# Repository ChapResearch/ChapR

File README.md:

# ChapR
The ChapR is a patented remote for controlling FTC, FLL, and FRC robots without a PC. It allows teams to easily set up drive practices and run autonomous programs without bothering the programmer(s) or fighting over the few PCs available. Created in 2013, it has been “sold” to hundreds of teams all over the world, using the “profits” to fund free ChapRs for teams in need. For more information on sales and usage of the device, see [the project website](http://thechapr.com). For more information on the creation of the device, see its [project page](http://chapresearch.com/?page_id=868).

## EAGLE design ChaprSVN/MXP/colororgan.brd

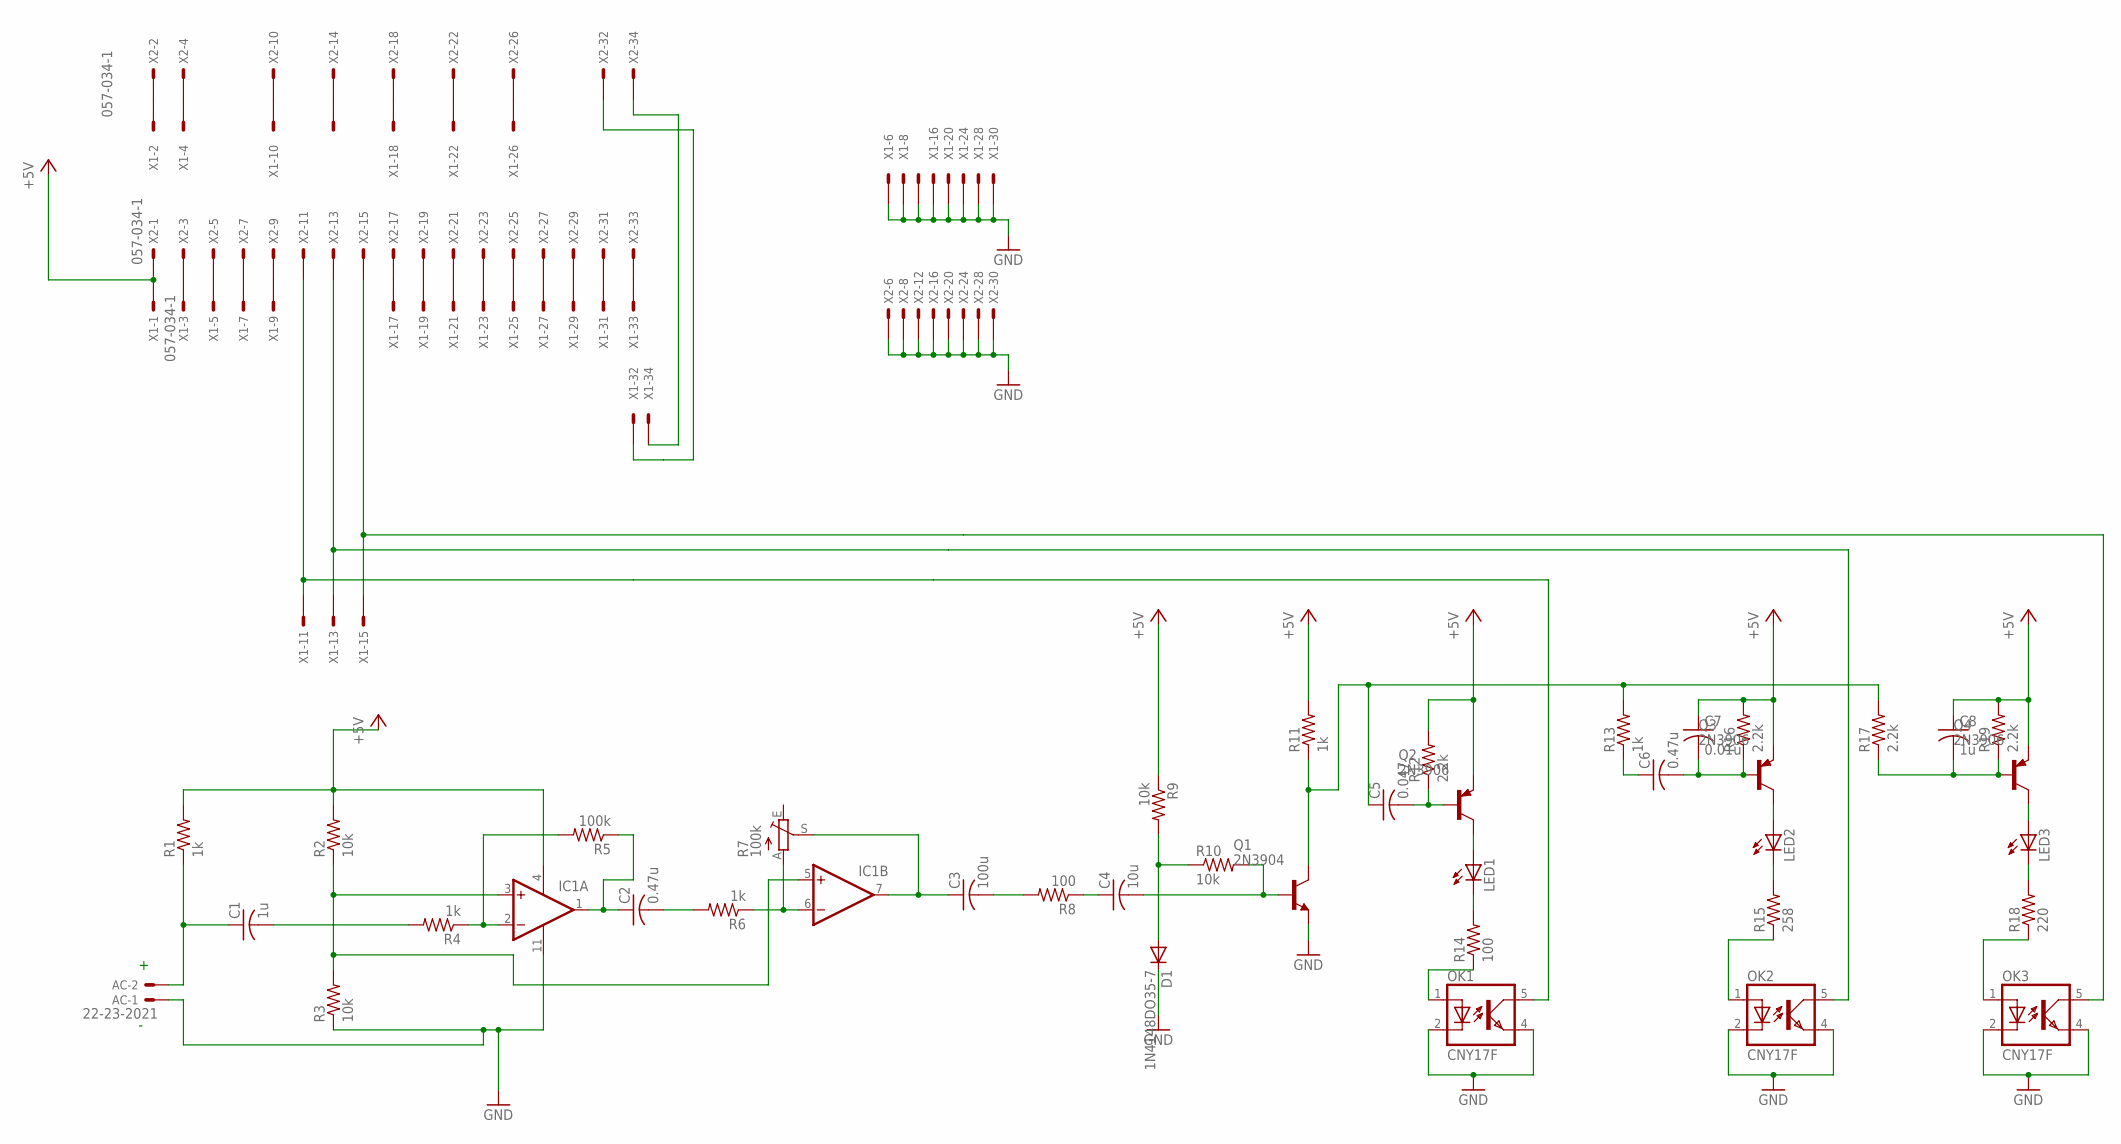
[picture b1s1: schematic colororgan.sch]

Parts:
AC: 22-23-2021
C1, C8: 1u; C025-050X050
C2, C6: 0.47u; C025-050X050
C3: 100u; C025-050X050
C4: 10u; C025-050X050
C5: 0.047; C025-050X050
C7: 0.01u; C025-050X050
D1: 1N4148DO35-7; DO35-7
IC1: LMV324THR; DIL14
LED1, LED2, LED3: LED3MM
OK1, OK2, OK3: CNY17F; DIL06
Q1: 2N3904; TO92
Q2, Q3, Q4: 2N3906; TO92
R1, R4, R6, R11, R13: 1k; 0207/10
R2, R3, R9, R10: 10k; 0207/10
R5: 100k; 0207/10
R7: 100k; RS3
R8, R14: 100; 0207/10
R12, R16, R17, R19: 2.2k; 0207/10
R15: 258; 0207/10
R18: 220; 0207/10
X1, X2: 057-034-1

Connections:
+5V: C7.1, C8.1, IC1.4 (V+), Q2.3 (E), Q3.3 (E), Q4.3 (E), R1.2, R2.2, R9.1, R11.2, R12.2, R16.2, R19.2, X1.1, X2.1
GND: AC.1, D1.C, IC1.11 (V-), OK1.2 (C), OK1.4 (EMIT), OK2.2 (C), OK2.4 (EMIT), OK3.2 (C), OK3.4 (EMIT), Q1.3 (E), R3.1, X1.6, X1.8, X1.12, X1.16, X1.20, X1.24, X1.28, X1.30, X2.6, X2.8, X2.12, X2.16, X2.20, X2.24, X2.28, X2.30
unnamed: AC.2, C1.1, R1.1
unnamed: D1.A, R9.2, R10.1
unnamed: C1.2, R4.2
unnamed: IC1.3 (+IN), IC1.5 (+IN), R2.1, R3.2
unnamed: IC1.2 (-IN), R4.1, R5.2
unnamed: C2.1, IC1.1 (OUT), R5.1
unnamed: C2.2, R6.2
unnamed: IC1.6 (-IN), R6.1, R7.A
unnamed: C4.2, Q1.2 (B), R10.2
unnamed: C3.1, IC1.7 (OUT), R7.S
unnamed: C3.2, R8.2
unnamed: C4.1, R8.1
unnamed: C5.1, Q1.1 (C), R11.1, R13.2, R17.2
unnamed: C5.2, Q2.2 (B), R12.1
unnamed: OK1.1 (A), R14.1
unnamed: LED1.K (C), R14.2
unnamed: LED1.A, Q2.1 (C)
unnamed: C6.1, R13.1
unnamed: C6.2, C7.2, Q3.2 (B), R16.1
unnamed: OK1.5 (COL), X1.11, X2.11
unnamed: LED2.A, Q3.1 (C)
unnamed: LED2.K (C), R15.2
unnamed: OK2.1 (A), R15.1
unnamed: OK2.5 (COL), X1.13, X2.13
unnamed: C8.2, Q4.2 (B), R17.1, R19.1
unnamed: LED3.A, Q4.1 (C)
unnamed: LED3.K (C), R18.2
unnamed: OK3.1 (A), R18.1
unnamed: OK3.5 (COL), X1.15, X2.15
unnamed: X1.34, X2.34
unnamed: X1.32, X2.32
unnamed: X1.2, X2.2
unnamed: X1.4, X2.4
unnamed: X1.10, X2.10
unnamed: X1.14, X2.14
unnamed: X1.33, X2.33
unnamed: X1.3, X2.3
unnamed: X1.5, X2.5
unnamed: X1.7, X2.7
unnamed: X1.9, X2.9
unnamed: X1.17, X2.17
unnamed: X1.19, X2.19
unnamed: X1.21, X2.21
unnamed: X1.23, X2.23
unnamed: X1.25, X2.25
unnamed: X1.27, X2.27
unnamed: X1.29, X2.29
unnamed: X1.31, X2.31
unnamed: X1.18, X2.18
unnamed: X1.22, X2.22
unnamed: X1.26, X2.26

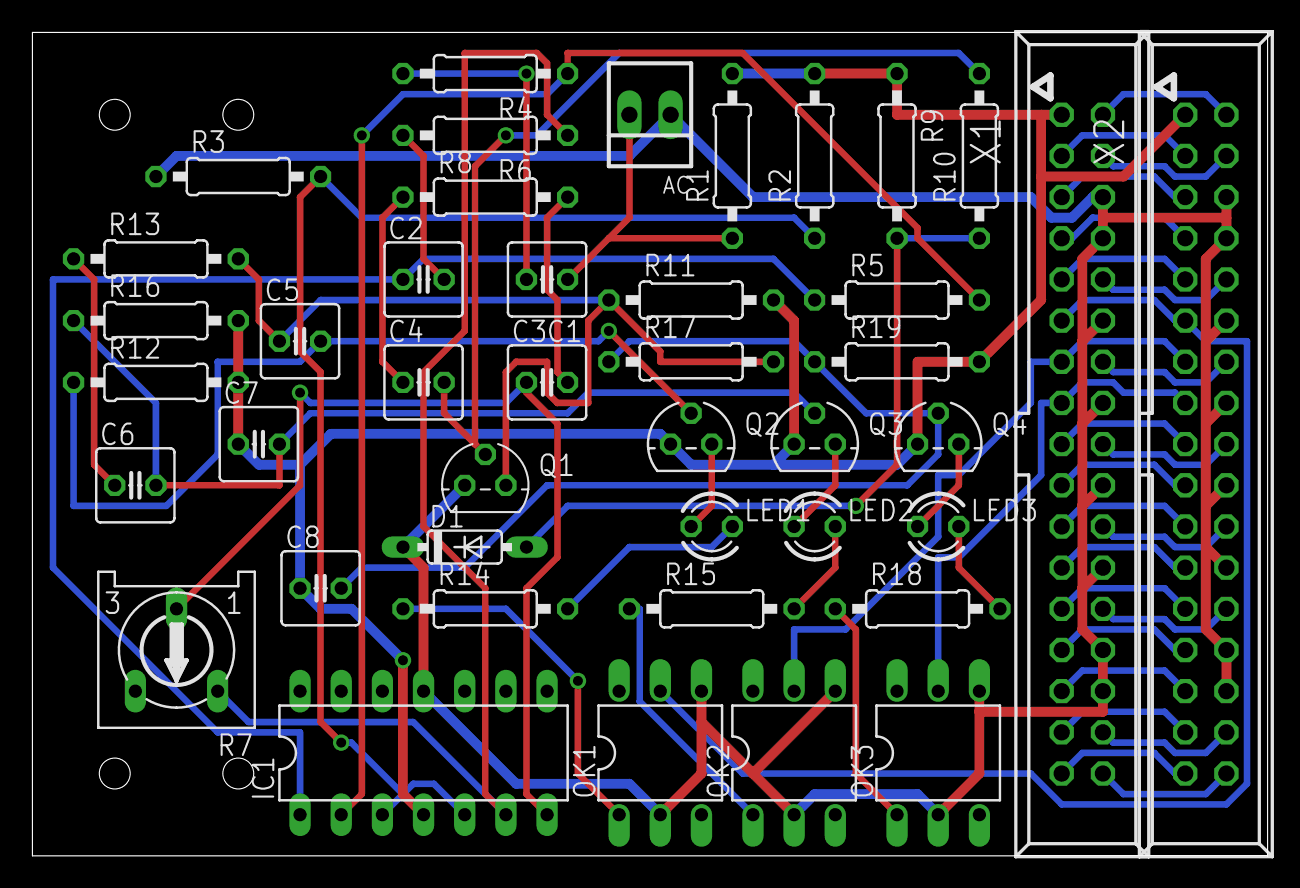
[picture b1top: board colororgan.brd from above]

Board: 2 copper layers, 76.2 x 50.8 mm, 42 parts (0 on the bottom side), 53 nets.

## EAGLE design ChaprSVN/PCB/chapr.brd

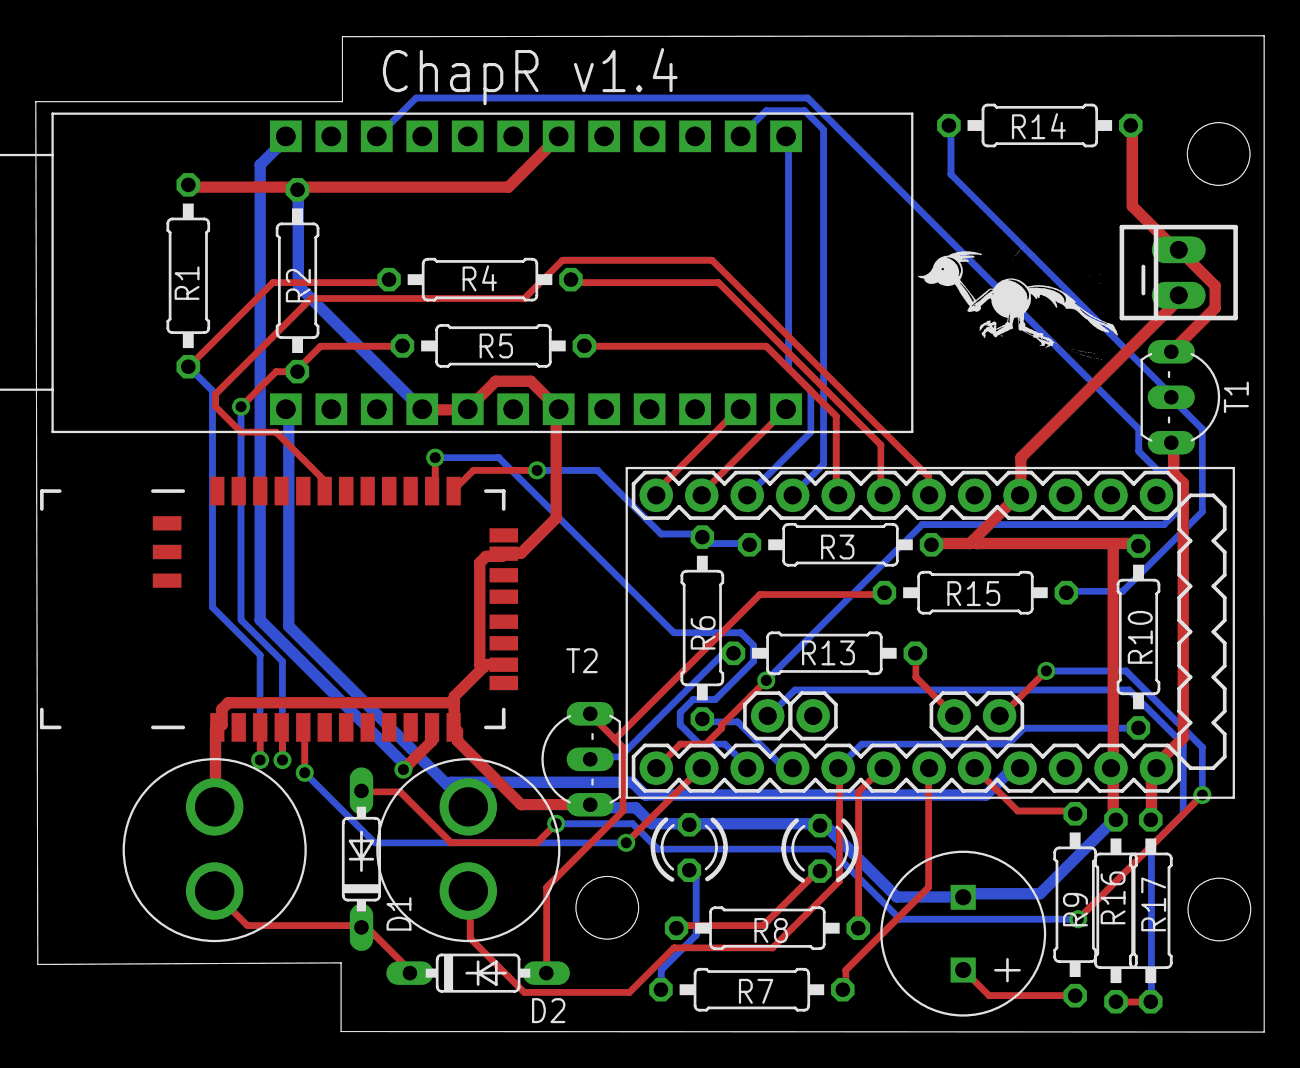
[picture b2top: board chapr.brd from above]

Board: 2 copper layers, 68.6 x 55.6 mm, 28 parts (0 on the bottom side), 33 nets.

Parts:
-: 9v power; 22-23-2021
ARDUINO: PROMININOHEADER
D1, D2: 1N4148; DO35-7
LED1: LED3MM
M2: RN42 Module; RN41
PB1: PUSHBUTTON; 2-PIN-PUSHBUTTON
PB2: BUTTON; 2-PIN-PUSHBUTTON
PWR-LED: LED3MM
R1, R2, R3, R14: 19.1k; 0207/10
R4, R5, R6, R10, R13: 10k; 0207/10
R7, R8: 470; 0207/10
R9: 100; 0207/10
R15: 1.5k; 0207/10
R16, R17: 24K; 0207/10
T1: 3906; TO92-EBC
T2: 3904; TO92-EBC
U$1: V2DIP2
U$2: SPEAKER

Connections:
+3V3: M2.11, U$1.P$24
+5V: ARDUINO.VCC, PB1.P$1, U$1.P$1
+9V: -.2, R14.2, T1.E
GND: -.1, ARDUINO.GND, ARDUINO.GND2, LED1.K, M2.1, M2.12, M2.28, M2.29, PB2.P$1, PWR-LED.K, R1.1, R2.1, R3.1, R10.1, R16.2, T2.E, U$1.P$4, U$1.P$5, U$1.P$7, U$1.P$18, U$2.-
unnamed: R14.1, R15.1, T1.B
unnamed: ARDUINO.D10, U$1.P$22
unnamed: ARDUINO.D13, R6.2
unnamed: ARDUINO.D12, M2.14
unnamed: ARDUINO.D11, M2.5
unnamed: M2.3, R1.2, R4.1
unnamed: M2.4, R2.2, R5.1
unnamed: ARDUINO.D5, R5.2
unnamed: M2.13, R3.2, R6.1
unnamed: ARDUINO.D6, U$1.P$14
unnamed: ARDUINO.D7, U$1.P$13
unnamed: ARDUINO.D8, U$1.P$12
unnamed: ARDUINO.D9, U$1.P$11
unnamed: ARDUINO.D4, R4.2
unnamed: ARDUINO.D3, M2.19
unnamed: PWR-LED.A, R7.1
unnamed: LED1.A, R8.1
unnamed: ARDUINO.A2, R7.2
unnamed: R9.1, U$2.+
unnamed: ARDUINO.A1, R8.2
unnamed: ARDUINO.A3, R9.2
unnamed: ARDUINO.RAWV, R17.1, T1.C
unnamed: ARDUINO.A0, PB1.P$2, R10.2
unnamed: D2.A, R15.2, T2.C
unnamed: R13.1, T2.B
unnamed: D1.C, D2.C, PB2.P$2
unnamed: ARDUINO.A5, D1.A
unnamed: ARDUINO.A4, R13.2
unnamed: ARDUINO.A6, R16.1, R17.2

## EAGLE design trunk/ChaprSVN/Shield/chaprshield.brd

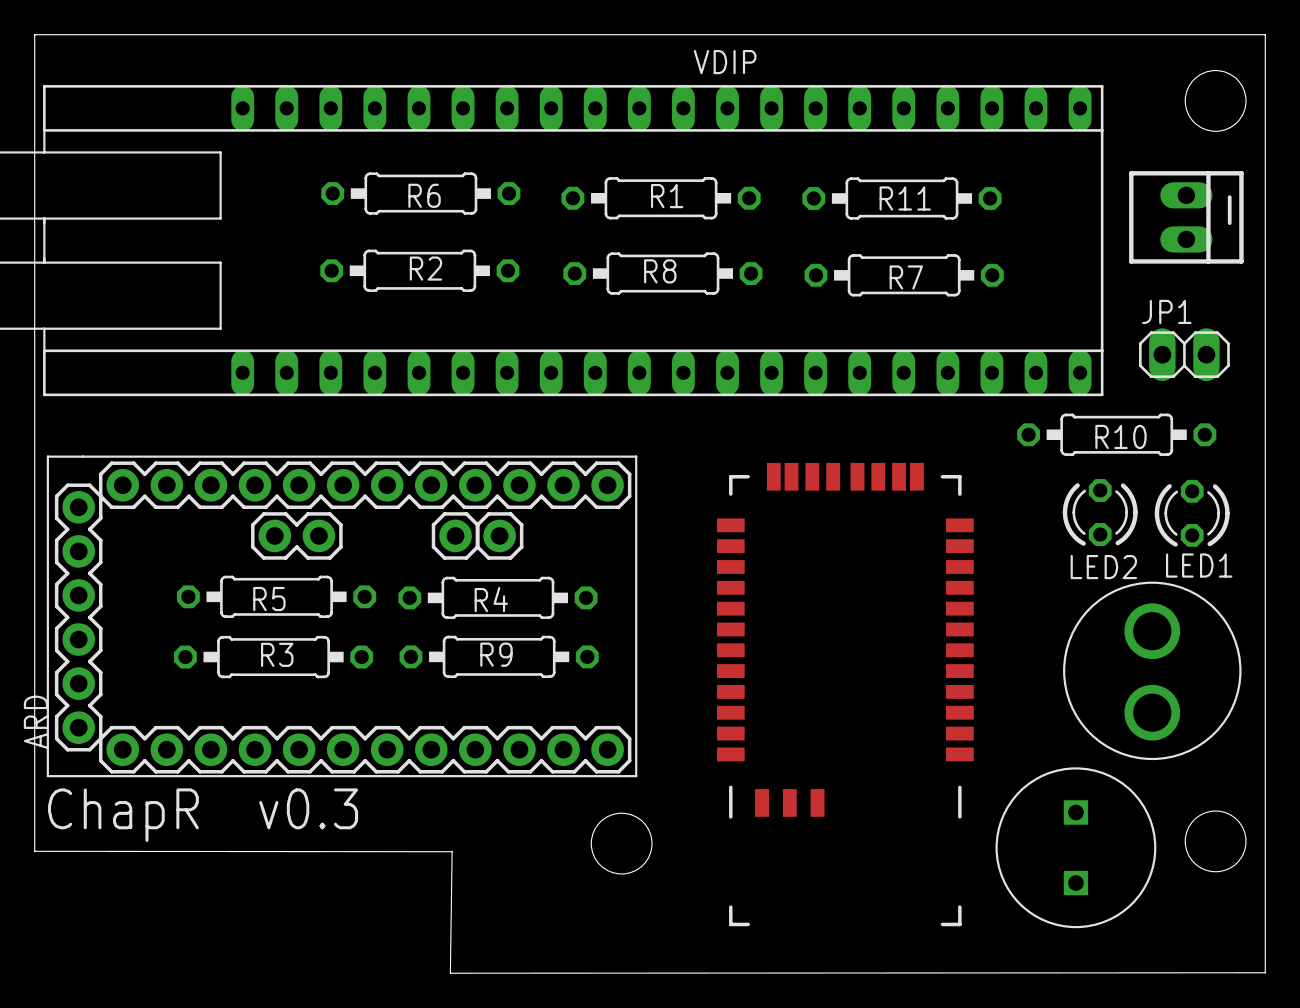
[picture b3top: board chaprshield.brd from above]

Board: 2 copper layers, 70.9 x 54.1 mm, 20 parts (0 on the bottom side), 26 nets, no tracks yet.

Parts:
-: 9v power; 22-23-2021
ARD: PROMINI
JP1: 1X02
LED1, LED2: LED3MM
M2: RN42 Module; RN41
PB1: PUSHBUTTON; 2-PIN-PUSHBUTTON
R1, R2, R3: 19.1k; 0207/10
R4, R5, R6, R10, R11: 10k; 0207/10
R7, R8: 470; 0207/10
R9: 100; 0207/10
U$2: SPEAKER
VDIP: VDIP2

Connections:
3.3V: JP1.2, M2.11, VDIP.32, VDIP.38, VDIP.39
+9V: -.2, ARD.RAWV
GND: -.1, ARD.GND, ARD.GND2, LED1.K, LED2.K, M2.1, M2.12, M2.28, M2.29, R1.1, R2.1, R3.1, R10.1, R11.1, U$2.-, VDIP.12, VDIP.13, VDIP.15, VDIP.26
unnamed: ARD.VCC, PB1.P$1, VDIP.2, VDIP.3, VDIP.9
unnamed: ARD.D10, VDIP.30
unnamed: ARD.D13, R6.2
unnamed: ARD.D12, M2.14
unnamed: ARD.D11, M2.5
unnamed: M2.3, R1.2, R4.1
unnamed: M2.4, R2.2, R5.1
unnamed: ARD.D5, R5.2
unnamed: M2.13, R3.2, R6.1
unnamed: ARD.D9, VDIP.18
unnamed: ARD.D8, VDIP.17
unnamed: ARD.D7, VDIP.16
unnamed: ARD.D6, VDIP.14
unnamed: ARD.D4, R4.2
unnamed: ARD.D3, M2.19
unnamed: LED2.A, R7.1
unnamed: LED1.A, R8.1
unnamed: ARD.A2, R7.2
unnamed: R9.1, U$2.+
unnamed: ARD.A1, R8.2
unnamed: ARD.A3, R9.2
unnamed: JP1.1, M2.22, R11.2
unnamed: ARD.A0, PB1.P$2, R10.2

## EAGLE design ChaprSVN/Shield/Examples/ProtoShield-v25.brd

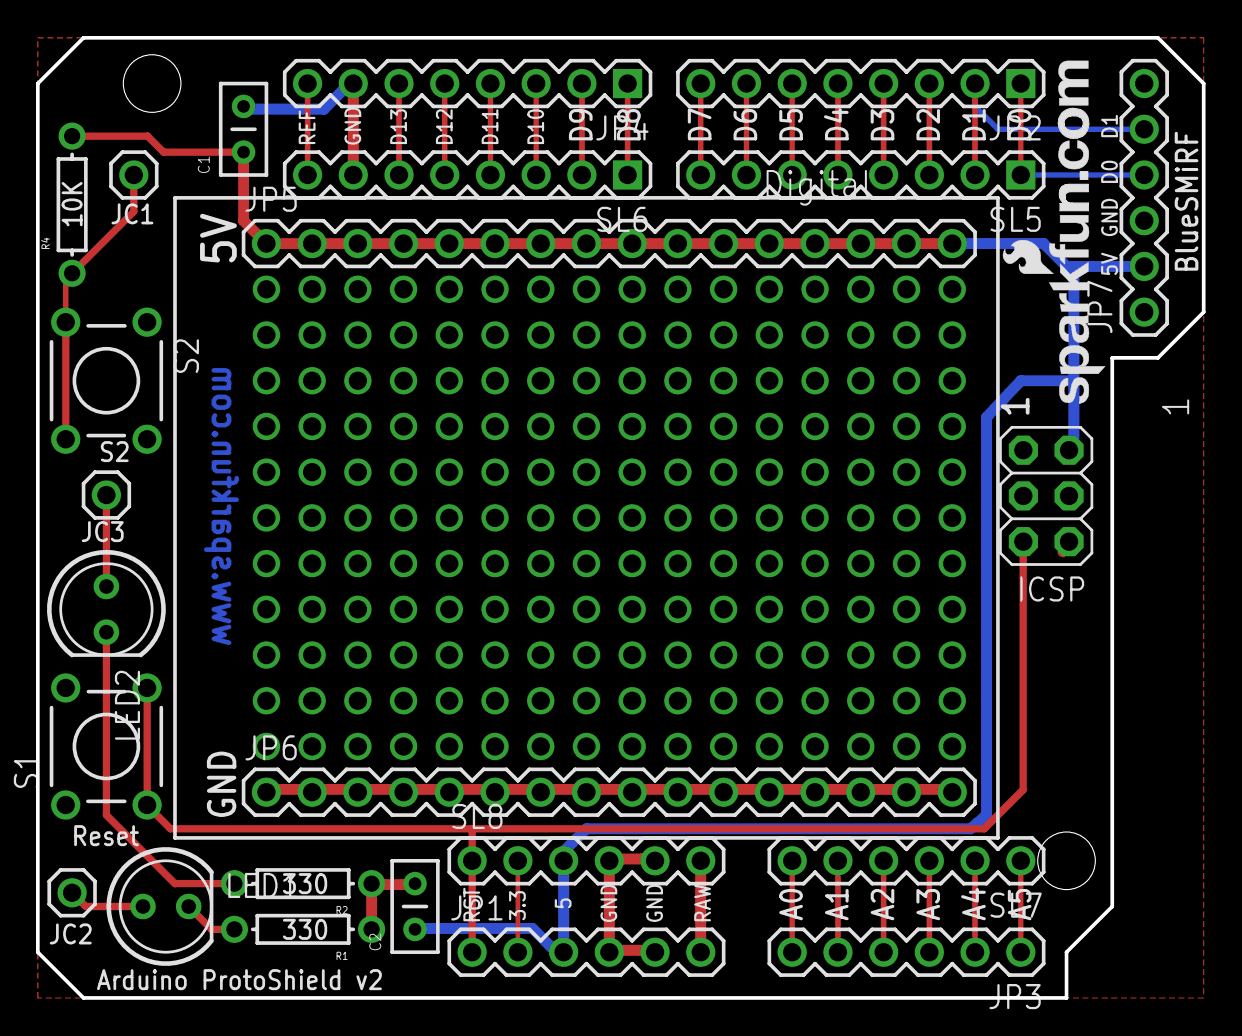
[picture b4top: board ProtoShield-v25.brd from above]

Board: 2 copper layers, 64.8 x 53.3 mm, 27 parts (0 on the bottom side), 31 nets.

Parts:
BB1: BREADBOARDMINI; BREADBOARD-MINI
C1, C2: 0.1uF; CAP-PTH-SMALL2
ICSP: ICSP; 2X03
JC1, JC2, JC3: M01PTH; 1X01
JP1: Power; 1X06
JP2: Digital1; 1X08
JP3: Analog; 1X06
JP4: Digital2; 1X08
JP5, JP6: M16PTH; 1X16
JP7: BlueSMiRF; 1X06
LED1, LED2: LED5MM
R1, R2: 330; AXIAL-0.3
R4: 10K; AXIAL-0.3
S1: Reset; TACTILE-PTH
S2: TACTILE-PTH
SL5, SL6: 1X08
SL7, SL8: 1X06
U$1: LOGO-SFENEW; SFE-NEW-WEBLOGO
U$2: CREATIVE_COMMONS

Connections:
3.3V: JP1.2, SL8.2
5V: C1.1, C2.1, ICSP.2, JP1.3, JP5.1, JP5.2, JP5.3, JP5.4, JP5.5, JP5.6, JP5.7, JP5.8, JP5.9, JP5.10, JP5.11, JP5.12, JP5.13, JP5.14, JP5.15, JP5.16, JP7.2, R4.P$2, SL8.3
A0: JP3.6, SL7.6
A1: JP3.5, SL7.5
A2: JP3.4, SL7.4
A3: JP3.3, SL7.3
A4: JP3.2, SL7.2
A5: JP3.1, SL7.1
AREF: JP4.8, SL6.8
D2: JP2.3, SL5.3
D3: JP2.4, SL5.4
D4: JP2.5, SL5.5
D5: JP2.6, SL5.6
D6: JP2.7, SL5.7
D7: JP2.8, SL5.8
D8: JP4.1, SL6.1
D9: JP4.2, SL6.2
D10: JP4.3, SL6.3
D11: JP4.4, SL6.4
D12: JP4.5, SL6.5
D13: JP4.6, SL6.6
GND: C1.2, C2.2, ICSP.6, JP1.4, JP1.5, JP4.7, JP6.1, JP6.2, JP6.3, JP6.4, JP6.5, JP6.6, JP6.7, JP6.8, JP6.9, JP6.10, JP6.11, JP6.12, JP6.13, JP6.14, JP6.15, JP6.16, JP7.3, R1.P$1, R2.P$1, S1.1, S1.2, S2.1, S2.2, SL6.7, SL8.4, SL8.5
unnamed: JC1.1, R4.P$1, S2.3, S2.4
unnamed: LED1.K, R1.P$2
unnamed: LED2.K, R2.P$2
unnamed: JC2.1, LED1.A
unnamed: JC3.1, LED2.A
RESET: ICSP.5, JP1.1, S1.3, S1.4, SL8.1
RX: JP2.1, JP7.4, SL5.1
TX: JP2.2, JP7.5, SL5.2
VIN: JP1.6, SL8.6

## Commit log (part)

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2014-05-20 Removed references to MODE coming from the main .ino loop. In personality 1 mode wasn't used anyway.
2014-05-20 Refactored mode stuff (now reads from EEPROM for normal setting and changes appropriately for matchMode)
2014-05-20 Removed references to the usermode (teleop/auto) leaving that for the personalities to deal with. It is still in EEPROM (settings), however.
2014-05-20 Finished refactoring.
2014-05-20 Got rid of all usermode stuff
2014-05-20 Refactoring done for real...maybe?
2014-05-20 Removed the zombie mode that we no longer used. Note that the code is in a NOTDEF in VDIP.cpp and BT.cpp so some future person can see how to enter zombie mode if they want.
2014-05-21 Adjusted The ChapR.vi to account for the new packet structure (incorporates analog and digital inputs).
2014-06-05 Implemented the match cycling in personality 0 and 3. Also added the rough drafts of documentation stuff. The Match Cycling Diagram.pptx is just meant to give an idea of whether or not we could make 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
2014-06-05 Moved the ChapR stuff out of this folder (so it would all be in one place, called by all test programs). NOT BEEN TESTED.
2014-06-05 ChapR Test files and ChapR Code in its own folder.
2014-06-05 Commented the ChapR Test code.
2014-06-06 Fixed the button translating in the ChapR.vi. Also made a small change to ChapR Test for debugging matchMode.
2014-06-06 Changed cRIO calls to require booleans specifying enable/mode for sending data to the cRIO (as opposed to having defines for the commands).
2014-06-06 Updated to remove the button from the Loop() call.
2014-06-07 Updated the Loop() function to NOT have the button. It doesn't affect this personality in any way.
2014-06-07 Removed the button from the Loop() function and recoded appropriately to use the "enabled" member of the personality object.
2014-06-10 Added new stuff to the back of my head.txt and some sketchy NXT Remote/Old Remote/Copy of client.c stuff...
2014-06-10 Combined the code for personalities 0 and 2 to save code space. 2 is just like 0 except that the action button toggles enabled.
2014-08-26 Added a ProMini version without the 6 pin header. The silk screen is still there so that it is easy to appropriately orient the ProMini, but this version doesn't cause the holes to be drilled, provid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
2014-08-26 Removed the extraneous library backup files.
2014-08-26 Used the new ProMini without the top 6 pins. Created AutoRouter and DesignRule files for repeatable routing. Added clearance between vias and pads so we don't have to post-process the routes.
2014-10-19 Added the ChapR Soldering Station List.doc
2014-10-25 Added ChapR Kit Instructions.docx
2014-11-05 Fixed a minor bug with the output saying the wrong status message.
2014-11-05 added LATEST (and hopefully last) endcap, with ALL relevant files
2014-12-19 Added the "chaprd" program for driving FRC bots with roboRIO.
2014-12-24 Added the SparkFun Blog Post.docx
2014-12-24 Added the full translation for chaprd.c
2014-12-27 latest version of chaprd - NOT working yet
2014-12-29 Added the Chap Research 2015 Kickoff Presentation.pptx.
2014-12-30 Latest (minor) edits.
2015-01-02 Made it so the daemon could start on boot. Still a problem with ejecting and re-plugging in the FirePlug.
2015-01-04 Ben's first cut at Eagle versions of the BeatBoard MXP board.
2015-01-04 A few changes for ease of reading. added 5v to the upward bound MXP connector.
2015-01-05 Added Makefile for building of the install file. Added install file template.
2015-01-06 It the Solo now works like it used to on the new board. It can detect different game modes now.
2015-01-07 Took the sleep statement out of the daemon. Adjusted the install shell script so that it doesn't change the permissions of the entire init.d (aka preventing lvrt from running important stuff).
2015-01-10 The latest fiddling around with getting the VDIP to set the BAUD rate on the FirePlug
2015-01-12 V2DIP2 Source as a reference for the VDIP source - this only has VDAP for now
2015-01-14 Added the Chap Research 2015 Kickoff Presentation and made slight modifications to the SparkFun Blog Post.docx
2015-01-14 Made minor edits to the QA info.
2015-01-15 The score reader works for 6 digit numbers... but it has a little problem with 5 digits.(should be relatively easy to fix though)
2015-01-16 Michael did something? Potentially bug testing. Evidently very minor.
2015-01-17 added a space
2015-01-18 added doPiano and sounds for it
2015-01-19 Made the final changes (this is the version that was submitted).
2015-01-19 The score playing system works. Just need to add sound files fore ten, eleven, and twelve.
2015-01-20 fixed wrong case vdip.h
2015-01-20 FirePlug programming integration - as well as a few optimizations
2015-01-20 forgot to update this when I updated VDIP.cpp
2015-01-20 added default in switch to quite compiler - an actually saved 14 bytes
2015-01-20 took out superficial .mp3 extension
2015-01-20 Made minor changes to fix the unsigned vs signed compiler warnings
2015-01-21 Added steps to test the new features of software v2.0
2015-01-21 Added piano mode
2015-01-21 saved a few bytes of memory by making explicit delay call
2015-01-21 fixed a few more compiler warnings
2015-01-22 added wiring diagram
2015-01-22 NOT FULLY WORKING - added matchmode and personality 0/2 implementation of it - turned off personality 3 for now
2015-01-22 personality 0/2 working first version of matchmode - not fully tested, but in pretty good shape.
2015-01-22 A couple fixes to personality 0/2, and a space rewrite of personality 1.
2015-01-23 Re-added the FTC LabView testing program (called teleop.vi).
2015-01-24 Make minor changes.
2015-01-25 Finished the Wiring Diagram.pptx
2015-01-27 renamed install file
2015-02-02 Added in boardBringUp and made memory optimization changes.
2015-02-03 Made minor edits to fix the bug about the ChapR not disabled when disconnected.
2015-02-04 Adjusted the wires that go to the analog pins on the Arduino.
2015-02-07 Added the Testing Programs and the end_plate stuff.
2015-02-07 The final copy that was discussed with Coach Eric, Coach Morgan, Rachel Gardner, Scott Gardner and Michael Huang.
2015-02-07 The "diff" feature doesn't work, so I'm not sure what changed, but ok. Probably something very small.
2015-02-08 Made the Chap Research Description.docx more aesthetically pleasing.
2015-02-08 Added the Arduino code for running the RN42 tester.
2015-02-10 Changes to bring the code under 30k bytes. Mostly to setup strings and the analog values.
2015-02-10 Added "!" starts up board bringup.
2015-02-10 Added RN42 test program that can cause an RN42 to print out version number on a completed ChapR - though you have to have a logic analyzer to see it!
2015-02-12 A bug in new magic new is still there. When played, the arduino senses a fruit being touched before you can touch the correct fruit.
2015-02-12 The latest and greatest almost working one.
2015-02-12 Done: analog triggers of Xbox 360 always send 0
    FTC personalities set by USB use FTC defaults for matchmode (same for FRC)
    *NOTE: this does NOT occur for the setting by Serial because it's so easy to set the values yourself, but I can change that if you think it's worth it
    matchmode noises (though I use beep and boop because there isn't space for new ones)
    To Do:
    auto enabled setting for roboRIO (asking Joe for the value)
    board bring up (checking VDIP and RN42 version)
2015-02-12 put contents of defaults onto the svn
2015-02-13 Fixed classic mode; working on piano mode
2015-02-13 made piano mode work
2015-02-14 Added "Documentation" folder to store items, added ChapX.pptx
2015-02-14 Potentially fixed a bug in VDIP.cpp, by changing the flagging loop to have 8 instead of 2 cycles. Got rid of some print lines in drivers.cpp.
2015-02-15 Made minor edits to the Presentation.pptx
2015-02-15 Added a print line to show where I want to call the clear() function in gamepad.cpp.
2015-02-16 Changed the i=8 to i=2 in the port cycling loop thing of VDIP.cpp. It may be fixed in another revision, but it was a bug we introduced when trying to fix the VDIP stuff.
2015-02-16 Took out digital and analog inputs, saving 3,000 bytes. However, this version may not work and we may want the ChapR to send this stuff for cRIO version, so they are probably going back in.
2015-02-16 Kept analog and digital inputs in. However, they have not been tested, and are only accessible through the Serial monitor. This version of the code has been well tested, but I will continue to test.
2015-02-17 Added the file extension, just to be precise.
2015-02-17 Nice comment for MatchReset()
2015-02-17 Changed the method by which USB port changes are "noticed." A new routine in VDIP.cpp uses the QP command to determine if something has changed on the USB ports. If so, then the longer deviceUpdate()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
2015-02-22 Fixed some minor bugs in match mode (timing, release of button).
2015-02-23 Added the SXSW submissions.
2015-02-25 Various typographic fixes, and slight content fixes.
2015-03-02 Re-added the FMV command for the VDIP (version check). It was removed when the board bring-up was removed. Also fixed a latent bug with closing VDIP files, which would only occur with filenames that 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
2015-03-10 Added the Chap Research Presentation for SXSW
2015-03-18 Added the various exchange program files.
2015-07-15 Added the sighup fix.
2015-07-15 Added chaprd magic calls and debug ones.
2015-07-19 Take 2 of adding sloth stuff in order to transfer to my Windows machine
2015-07-22 Take 1 at obliterating all analog and digital inputs.
2015-07-22 Take 2 of getting rid of analog and digital values as a setting on the ChapR.
2015-07-25 Finished adding bits and pieces to allow for FRC compatibility.
2015-07-31 Added stuff to make v1 work. Now into initial testing (minus the TCP descriptors).
2015-08-24 Cleaning up repository to include only useful ChapR stuff.
2015-09-10 chaprd.c
2015-09-10 Adding the install script for the daemon.
2015-09-14 Adding this file for testing purposes.
2015-09-14 Testing 2
2015-10-10 Changed version to v.2 and took out some Serial print lines within the VDIP code.
2015-10-20 Added a timeout an optional sleep to the reading of the USB.
2015-10-20 Deleted the unneccessary promotional materials for the ChapR. They have been moved to the Google Drive.
2015-10-20 Deleted the pictures folder, as all contents have been moved to the Google Drive.
2015-10-20 Moved files to google drive and cleaned up Chaprd.c Chaprd.c is working except for mysterious lag and joystick issue
2015-10-29 Changed the ChapR defaults to be for FRC.
2015-10-31 Deleted ChapX Folder
    These files have all been moved to a separate repository.
2015-11-11 Checkpoint on the path of crazy Linux watchdog stuff. For the purpose of testing only. THIS DOES NOT WORK PROPERLY.
2015-11-11 Another stage of somewhat working.
2015-11-13 Fixed the final issues with the watchdog. It appears to be bug free!
2015-11-18 After much mysteriousness, it appears to be working. Still looking into the causes of the original issue.
2015-11-19 Added last fixes to the ChapR 2.0 code
    Added the kill noise for the red button; caused the black button to kill
    programs
2015-11-20 Beautified the last little bits of the ChapR daemon to be beta tested; fixed the corrupted repository.
2016-01-08 Quick Clean-Up
    Moved some files to internal Google Drive folder.
2016-07-24 Added the cdebug binary for testing purposes.
2016-08-07 Added pairing utility to allow the user to automatically create a textfile to pair with the KC4134
2016-08-23 Updated the configUSBDongle.c to have longer waits between prints and more user-friendly messages

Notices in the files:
parts and their libraries:
SparkFun-RF: Licensing: CC v3.0 Share-Alike You are welcome to use this library for commercial purposes.
SparkFun: Released under the Creative Commons Attribution Share-Alike 3.0 License
SparkFun: http://creativecommons.org/licenses/by-sa/3.0
